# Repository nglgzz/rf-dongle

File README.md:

# RF Dongle

USB type-A dongle based on the nRF52840 microcontroller.

This dongle is meant to run the [COB firmware](https://github.com/nglgzz/cob_firmware),
though technically you can flash whatever you want on it.

## Current state

**What works**

- The dongle can be programmed through the SWD pads exposed on the back of the
  PCB.
- Debugging the microcontroller while it runs also works, through the same SWD
  pads.
- LEDs and reset buttons work.
- The chip antenna works and has a good range. I haven't tested its limit, but I
  tried both sending and receiving packets across a room (5-ish meters with a
  wall in between) and it worked fine and that's more than enough for my
  application.
- USB power is working, the device gets detected by the host, and it can
  enumerate as a HID device (haven't tried other USB 2.0 classes, but they
  should in theory work).

**What needs improvement**

- The USB connector (PCB trace) is quite thin, and in some USB ports it doesn't
  make a solid connection. One workaround is to add some tape on the underside
  of the PCB to increase its thickness. Need to figure out a neater solution
  though.

## Pics

This is the manufactured PCB (at [this commit](https://github.com/nglgzz/rf-dongle/tree/d430271ced6d7d4ebfe34358b9420bd28b8e23bf)).
The component pads are designed to make it easier to hand solder the components,
which is what I did.

<br/>

Below is the test jig I'm using to program and debug the dongle. I hacked this
together with a perforated board, a few pogo pins, and battery connectors I had
lying around.

<br/>

## Contributing

If you (unlike me) know what you're doing, and have tips for my circuit design,
please create an issue and tell me about it 🙏

## Learning

If you're curious about my learning journey with this project, I've documented
that [here](./LEARNING.md).

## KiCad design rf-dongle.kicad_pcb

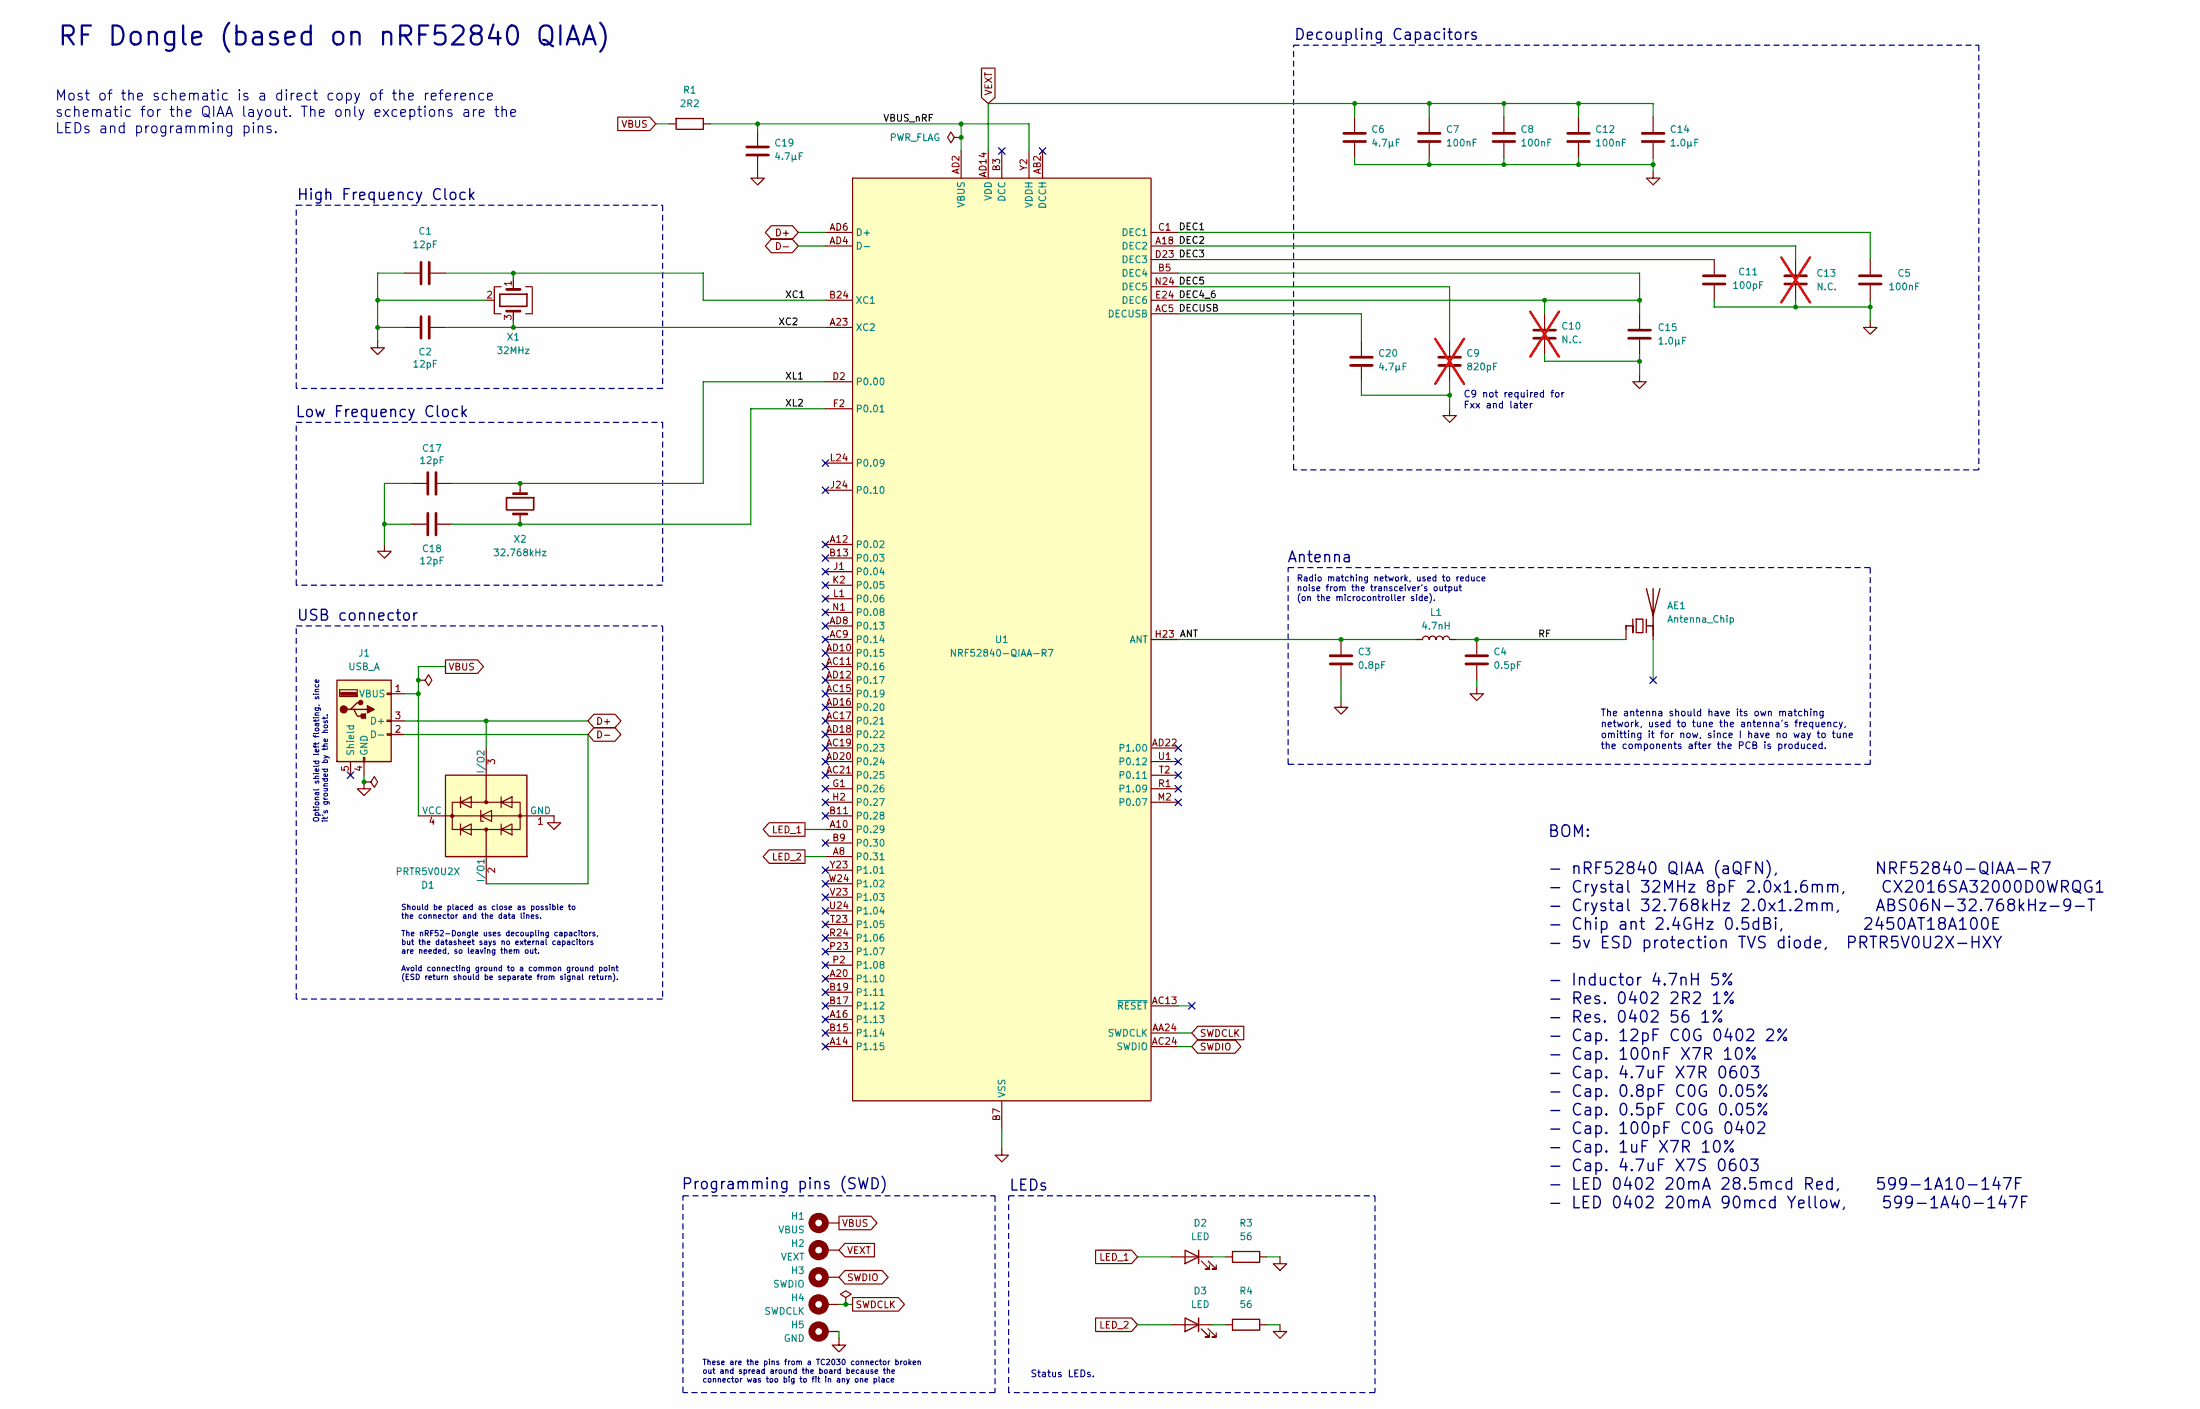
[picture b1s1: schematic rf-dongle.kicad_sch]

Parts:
AE1: Antenna_Chip; Johanson_2450AT18x100; JLC PN C89334
C1, C2, C17, C18: 12pF; C_0402_1005Metric_Pad0.74x0.62mm_HandSolder
C3: 0.8pF; C_0402_1005Metric_Pad0.74x0.62mm_HandSolder
C4: 0.5pF; C_0402_1005Metric_Pad0.74x0.62mm_HandSolder
C5, C7, C8, C12: 100nF; C_0402_1005Metric_Pad0.74x0.62mm_HandSolder
C6, C19, C20: 4.7µF; C_0603_1608Metric_Pad1.08x0.95mm_HandSolder
C9: 820pF; C_0402_1005Metric_Pad0.74x0.62mm_HandSolder; not fitted
C10, C13: N.C.; C_0402_1005Metric_Pad0.74x0.62mm_HandSolder; not fitted
C11: 100pF; C_0402_1005Metric_Pad0.74x0.62mm_HandSolder
C14, C15: 1.0µF; C_0603_1608Metric_Pad1.08x0.95mm_HandSolder
D1: PRTR5V0U2X; SOT-143; JLC PN C5337179
D2: LED; LED_0402_1005Metric_Pad0.77x0.64mm_HandSolder; JLC PN C165980
D3: LED; LED_0402_1005Metric_Pad0.77x0.64mm_HandSolder; JLC PN C165979
H1: VBUS; TestPoint_THTPad_D1.0mm_Drill0.5mm
H2: VEXT; TestPoint_THTPad_D1.0mm_Drill0.5mm
H3: SWDIO; TestPoint_THTPad_D1.0mm_Drill0.5mm
H4: SWDCLK; TestPoint_THTPad_D1.0mm_Drill0.5mm
H5: GND; TestPoint_THTPad_D1.0mm_Drill0.5mm
J1: USB_A; PCB_USB_connector
L1: 4.7nH; L_0402_1005Metric_Pad0.77x0.64mm_HandSolder
R1: 2R2; R_0402_1005Metric_Pad0.72x0.64mm_HandSolder
R3, R4: 56; R_0402_1005Metric_Pad0.72x0.64mm_HandSolder; JLC PN C784160
U1: NRF52840-QIAA-R7; Nordic_AQFN-73-1EP_7x7mm_P0.5mm; JLC PN C1851953
X1: 32MHz; Crystal_SMD_2016-4Pin_2.0x1.6mm
X2: 32.768kHz; Crystal_SMD_2012-2Pin_2.0x1.2mm_HandSoldering; JLC PN C97603

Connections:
/ANT: C3.2, L1.1, U1.H23 (ANT)
/DEC1: C5.1, U1.C1 (DEC1)
/DEC2: C13.1, U1.A18 (DEC2)
/DEC3: C11.1, U1.D23 (DEC3)
/DEC4_6: C10.2, C15.2, U1.B5 (DEC4), U1.E24 (DEC6)
/DEC5: C9.2, U1.N24 (DEC5)
/DECUSB: C20.2, U1.AC5 (DECUSB)
/RF: AE1.1 (FEED), C4.2, L1.2
/VBUS_nRF: C19.2, R1.1, U1.AD2 (VBUS), U1.Y2 (VDDH)
/XC1: C1.2, U1.B24 (XC1), X1.1
/XC2: C2.1, U1.A23 (XC2), X1.3
/XL1: C17.2, U1.D2 (P0.00), X2.1
/XL2: C18.1, U1.F2 (P0.01), X2.2
D+: D1.3 (I/O2), J1.3 (D+), U1.AD6 (D+)
D-: D1.2 (I/O1), J1.2 (D-), U1.AD4 (D-)
GND: C1.1, C2.2, C3.1, C4.1, C5.2, C6.1, C7.1, C8.1, C9.1, C10.1, C11.2, C12.1, C13.2, C14.1, C15.1, C17.1, C18.2, C19.1, C20.1, D1.1 (GND), H5.1, J1.4 (GND), R3.1, R4.1, U1.B7 (VSS), U1.EP (VSS), U1.F23 (VSS_PA), X1.2 (G), X1.4 (G)
LED_1: D2.2 (A), U1.A10 (P0.29)
LED_2: D3.2 (A), U1.A8 (P0.31)
unnamed: D2.1 (K), R3.2
unnamed: D3.1 (K), R4.2
SWDCLK: H4.1, U1.AA24 (SWDCLK)
SWDIO: H3.1, U1.AC24 (SWDIO)
VBUS: D1.4 (VCC), H1.1, J1.1 (VBUS), R1.2
VEXT: C6.2, C7.2, C8.2, C12.2, C14.2, H2.1, U1.A22 (VDD), U1.AD14 (VDD), U1.AD23 (VDD), U1.B1 (VDD), U1.W1 (VDD)

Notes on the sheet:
Antenna
RF Dongle (based on nRF52840 QIAA)
Decoupling Capacitors
LEDs
Radio matching network, used to reduce noise from the transceiver's output (on the microcontroller side).
Status LEDs.
C9 not required for Fxx and later
The antenna should have its own matching network, used to tune the antenna's frequency, omitting it for now, since I have no way to tune the components after the PCB is produced.
BOM: - nRF52840 QIAA (aQFN), NRF52840-QIAA-R7 - Crystal 32MHz 8pF 2.0x1.6mm, CX2016SA32000D0WRQG1 - Crystal 32.768kHz 2.0x1.2mm, ABS06N-32.768kHz-9-T - Chip ant 2.4GHz 0.5dBi, 2450AT18A100E - 5v ESD protection TVS diode, PRTR5V0U2X-HXY - Inductor 4.7nH 5% - Res. 0402 2R2 1% - Res. 0402 56 1% - Cap.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
Low Frequency Clock
USB connector
These are the pins from a TC2030 connector broken out and spread around the board because the connector was too big to fit in any one place
Optional shield left floating, since it's grounded by the host.
Most of the schematic is a direct copy of the reference schematic for the QIAA layout. The only exceptions are the LEDs and programming pins.
Should be placed as close as possible to the connector and the data lines. The nRF52-Dongle uses decoupling capacitors, but the datasheet says no external capacitors are needed, so leaving them out. Avoid connecting ground to a common ground point (ESD return should be separate from signal return).
Programming pins (SWD)
High Frequency Clock

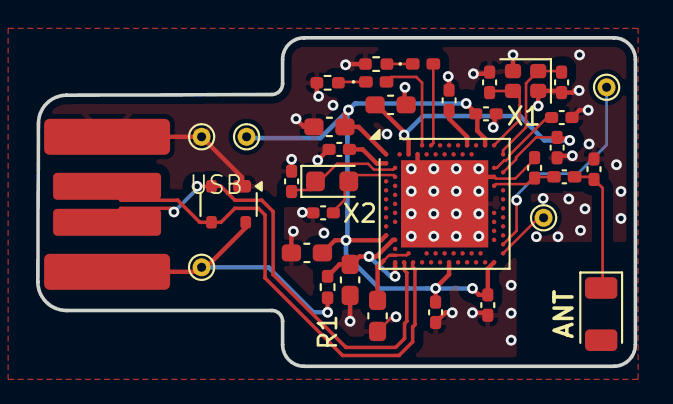
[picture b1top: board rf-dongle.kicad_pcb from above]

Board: 4 copper layers, 33.2 x 18.2 mm, 35 parts (0 on the bottom side), 23 nets.

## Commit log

2025-07-21 second attempt at routing
2025-07-21 rework programming pins, cleanup pcb routing
2025-07-21 adjust footprints for handsoldering, tweak antenna
2025-07-21 add first draft of schematic
2025-07-21 before new programming pins
2025-07-21 setup constraints, first attempt at routing
2025-07-21 add rough pcb layout
2025-07-21 setup pcb stackup
2025-07-21 add jobset
2025-07-21 adjust silkscreen
2025-07-21 ordered rev 1
2025-07-29 update product numbers and bom
2025-09-16 add learning resources
2025-09-21 cleanup USB routing, add JTAG contacts
    also remove unused components and swap reset button for programmable button
2025-09-21 ordered rev 2
2026-03-28 reverse USB pads and remove unnecessary component
2026-04-03 ordered rev 3
2026-04-03 ordered rev 3
    Reverted PCB outline to first iteration, swapped order of USB pads,
    removed an optional component near the antenna, and moved around
    debug pins to more easily align them with the perforated board
    used to create the programming jig.
2026-04-03 remove USB pads from solder paste layer (again)
